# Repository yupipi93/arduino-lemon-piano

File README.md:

<div align="center">

# 🍋 Super Lemon Piano

**Seven lemons, an Arduino Nano and a secret Mario melody.**
A 2019 university project, rescued in 2026 and still growing — nine boards, a
fabricable PCB, a printed case, and a firmware that is tested on a fake board
before it ever touches fruit.

</div>

---

## What it is

Hold a ground clip in one hand and touch a lemon with the other: your body closes
the circuit, the pin drops **three or four ADC counts**, and a note sounds. Seven
lemons make a keyboard. Each of the **four levels** hides a ten-note Mario melody
— the game plays you the hook, you find the notes, and ten green LEDs count how
close you are. Get it and the whole theme plays as a celebration; miss and the bar
blanks and you start that level again. There is also a fifth mode with no game in
it at all, where the lemons are simply *do re mi fa sol la si*.

The repo is organised as **one directory per hardware revision, all of them
active**. Nothing is archived: a bare-buzzer bring-up rig, the 2019 banana-piano
original, the water-pump build that was handed in at university, and today's
filtered ten-LED board each keep their own firmware, wiring diagram, emulation and
docs — and each is expected to build.

| Read | For |
|---|---|
| [**USER-GUIDE.md**](docs/USER-GUIDE.md) · [en español](docs/GUIA-DE-USO.es.md) | Playing it. The printable sheet — no electronics in it |
| [**versions/**](versions/) | The nine boards, what changed between them, and why |
| [**pcb/**](pcb/) | The fabricable KiCad 9 board, its renders and its gerbers |
| [**docs/HARDWARE.md**](docs/HARDWARE.md) | Touch physics, the polarity flip, the shared parts |
| [**docs/MARIO-SOUNDS.md**](docs/MARIO-SOUNDS.md) | Every melody and effect, with its provenance |
| [**docs/cartilla/**](docs/cartilla/) | The one-page folded booklet an organiser carries to an event |
| [**CHANGELOG.md**](CHANGELOG.md) · [TODO.md](TODO.md) | What changed, and what is still open |

---

## The thing itself

<div align="center">

<br/><em><b>SUPER LEMON PIANO</b> — printed case, ten-LED bar, passive buzzer behind the grille,<br/>two sensitivity buttons on the front, and a ribbon cable out to the fruit.</em>
</div>

<table>
<tr>
<td width="50%">

<br/><em>The ten LEDs run red → yellow → green, so how far you are is readable across a room. Left of the Nano: the 470 µF halves of the CLC pi filter.</em>
</td>
<td width="50%">

<br/><em>Seated in the case, with the Multitec logo embossed in the print. The ribbon leaves through a slot so the lid closes on a working piano.</em>
</td>
</tr>
</table>

### The PCB

<div align="center">

<br/><em>v0.7.1, top — LEDs north, keys south, Nano socketed with the USB facing west.</em>
<br/><br/>

<br/><em>Bottom — a full ground pour, and every 220 Ω pull-up on B.Cu.</em>
</div>

<div align="center">

<br/><em>Back from the fab house. <b>Created with ♥ by Multitec.</b></em>
</div>

---

## How it plays

1. **Power on.** The bar counts up while the firmware measures what *untouched*
   looks like on every lemon and derives the touch margin from the noise it finds.
   **Lights running = hands off the fruit.**
2. **It announces the level** with seven notes of that level's theme — and only
   notes your lemons can make (see *Three sizes of every song* below).
3. **Play.** Hold the GND clip, touch a lemon. The note sounds and holds for as
   long as you hold the fruit.
4. **Find the ten-note code.** Each correct note lights the next green LED. A
   wrong note blanks all ten and that level restarts. Nothing is punished until
   you have found the first note, so you can explore freely.
5. **Light all ten** and the level's **whole theme** plays as a celebration, then
   the flagpole fanfare, then the next level announces itself.
6. **Forgotten the tune?** **Tap the same lemon five times** and it plays again.

### The gestures

| Gesture | What it does |
|---|---|
| **tap +** / **tap −** | one step more / less sensitive — the bar shows where the knob sits |
| **hold + for 3 s** | switch between **free play** and the level you were on |
| **hold − for 3 s** | open the **mode wheel**: turn with + / −, accept with both buttons |
| **both buttons, 1 s**, while touching a lemon | **smart adjust** — learn the best margin from that real touch |
| **the same lemon ×5** | **play the level's tune again**. The note you just played counts as the first, so it is four more taps. It changes nothing: repeats never score |

### Free play

Hold **+** for three seconds and the game gets out of the way: the seven lemons
become `do re mi fa sol la si` (C5–B5), there is no code and no wrong note, and
**the same lemon may be played over and over** — which is exactly what the game
forbids, and exactly what an instrument is for.

The bar in free play **only ever moves**. Entering runs a sweep: two lights walk
in from the ends of the bar, meet in the middle, open back out until all ten are
lit, and go out. After that it is dark, and every note breaks a **wave** from that
lemon's own place on the bar — lemon 1 sends it left to right, lemon 7 right to
left, a lemon in the middle opens it both ways at once. Hold two lemons together
and both notes sound: one buzzer cannot hold two frequencies, so the voices swap
it every 10 ms, fast enough that the ear hears an interval instead of an
alternation.

### Three sizes of every song

Each theme exists at three lengths, because three different moments need three
different things:

| Size | Where | What it is |
|---|---|---|
| **Short** | the mode wheel | eight notes. Browsing four modes has to be fast |
| **Playable** | the level announcement, and the five-tap reminder | **seven notes, and only notes that level's lemons can make** |
| **Full** | the celebration when a level is cleared | the whole piece, 10–23 s |

The middle one is the clue, so it must not be full of notes the keyboard cannot
answer with — every theme reaches pitches that are on no lemon. The firmware
walks the theme, plays only what the level's row contains, and turns anything
else into silence of the same length so the rhythm of the hook survives. It lands
on each theme's actual hook, which is a pleasant accident of how Mario wrote them:

| Level | Theme | What it announces | The seven lemons, low → high |
|---|---|---|---|
| 1 | Overworld | `E7 E7 E7 C7 E7 G7 G6` — the riff, exactly | E6 G6 A6 B6 C7 E7 G7 |
| 2 | Underworld | `C4 C5 A3 A4 AS3 AS4 C4` | A3 AS3 C4 D4 A4 AS4 C5 |
| 3 | Starman | `C6 F5 F5 D5 F5 F5 D5` | C5 D5 E5 F5 G5 A5 C6 |
| 4 | Castle | `G3 D4 G3 D4 AS3 D4 AS3` — the pedal | G3 AS3 C4 D4 DS4 F4 G4 |

**Every lemon on every level is a note that level's own theme plays.** That is a
rule with a test behind it, not a convention — it was broken on levels 2, 3 and 4
until 2026-09-15, and level 4 answered a G-minor theme with a C major scale an
octave up.

<details>
<summary><b>The four secret codes (spoilers)</b></summary>

<br/>

Lemons numbered 1–7, left to right — lemon 1 is the one that sounds **lowest**.

| Level | Theme | Code |
|---|---|---|
| 1 | Super Mario Bros — Overworld | `6 · 5 · 6 · 7 · 2 · 5 · 2 · 1 · 3 · 4` |
| 2 | Super Mario Bros — Underworld | `3 · 6 · 1 · 4 · 2 · 5 · 3 · 6 · 1 · 4` |
| 3 | Super Mario Bros — Starman | `2 · 4 · 6 · 1 · 5 · 3 · 7 · 4 · 2 · 6` |
| 4 | Super Mario Bros — Castle | `5 · 1 · 3 · 7 · 2 · 6 · 4 · 1 · 5 · 3` |

Clear all four and the game-complete piece loops until you hold both buttons.

These numbers are **never typed by hand**. A level's code lives in the firmware as
note *frequencies*, and which lemon plays which note differs per level, so the
answer exists nowhere in the source. [`docs/cartilla/seqs.py`](docs/cartilla/seqs.py)
resolves one table against the other, cross-checks level 1 against a sequence the
host test declares independently, and exits non-zero rather than guess.

</details>

---

## The modes, as a machine

```mermaid
stateDiagram-v2
    direction LR
    state "FREE PLAY<br/>do re mi fa sol la si" as FreePlay
    state "MODE WHEEL<br/>four levels, previewed" as Wheel

    [*] --> Calibrate
    Calibrate --> Game : margin from measured noise

    state "GAME" as Game {
        [*] --> Level1
        Level1 --> Level2 : all ten LEDs
        Level2 --> Level3 : all ten LEDs
        Level3 --> Level4 : all ten LEDs
        Level4 --> Ending : all four cleared
        Ending --> Level1 : both buttons 1 s
    }

    Game --> FreePlay : hold + for 3 s
    FreePlay --> Game : hold + for 3 s
    Game --> Wheel : hold − for 3 s
    Wheel --> Game : both buttons = accept
    Wheel --> Game : long press = cancel
```

Free play is **chosen, never earned**: winning cycles 1 → 2 → 3 → 4 → 1 and never
lands on it.

---

## Hardware

<div align="center">

<br/><em>Every wiring diagram in this repo is <b>generated</b>, never hand-placed — see below.</em>
</div>

### Pin map (V5.5)

| Pin | What | Notes |
|---|---|---|
| `A0`–`A6` | lemon keys 1–7 | 220 Ω pull-up each; the player holds the **GND** clip |
| `D2`–`D11` | the ten-LED bar | LED *n* on pin *n+1* — nothing to look up |
| `D12` | **SENS +** button | to GND, internal pull-up |
| `A7` | **SENS −** button | analog-in only, so an external 10 kΩ pull-up; read as `< 512` |
| `D13` | passive buzzer | the Nano's own LED blinks with the audio, for free |

Needs a **Nano or Mini**: A6 is a key and A7 is a button, and the classic Uno
exposes neither.

### The board

| | |
|---|---|
| **Outline** | 120 × 40 mm, 2-layer FR4, 4 × M2 mounting |
| **MCU** | Arduino Nano, socketed, centred, mini-USB facing west |
| **Display** | 10 × Ø3 mm LEDs, north edge — 3 green, 3 yellow, 2 orange, 2 red |
| **Keys** | 1×8 header on the south edge, silk reads `KEYS 1 2 3 4 5 6 7 G` |
| **Sound** | passive buzzer + an `SPK` aux header in parallel with it |
| **Power** | `5V IN` → P6KE6.8A TVS → 1N5817 → 470 µF‖100 nF → 100 µH → 470 µF‖100 nF |
| **Status** | v0.7.1 — DRC 0/0/0, ERC 0/0, placement 74/0, geometry gate 30/30 |
| **Fab** | [`pcb/releases/v0.7.1/`](pcb/releases/v0.7.1/) — gerbers, drill, BOM, positions |

<details>
<summary><b>Why there is a filter on a 5 V input at all</b></summary>

<br/>

A touch is **3–4 ADC counts, about 15–20 mV** — skin is roughly 1 MΩ against a
220 Ω pull-up, which is a very lopsided divider. The +5 V rail is simultaneously
the top of all seven pull-ups **and AVcc, the ADC's own reference**. A slow sag
cancels out, because the ADC is ratiometric and baseline and reading move
together. A **fast edge does not**: the pin node sits behind 220 Ω and wire
capacitance while the reference goes straight into AVcc, so the two move at
different speeds and the difference lands squarely inside a 15 mV margin.

Which is not theory. A light switch elsewhere in the house played phantom notes.
The filter (TVS + Schottky + CLC pi, fc ≈ 730 Hz) is V5.5's entire hardware
delta; the game and the firmware pinout are V5's, untouched.

Full derivation: [`versions/v5.5-power-filter/HARDWARE.md`](versions/v5.5-power-filter/HARDWARE.md).
Running it off a battery instead: [`docs/POWER-FROM-A-POWER-BANK.md`](docs/POWER-FROM-A-POWER-BANK.md).

</details>

---

## Quick start

```bash
# PlatformIO CLI, once
pipx install platformio                 # or: pip install --user platformio

cd versions/v5.5-power-filter/firmware  # ...or any other version's firmware/
pio run                                 # build  (default: nanoatmega328)
pio run -t upload                       # flash the Nano
pio device monitor                      # 9600 baud — the game logs what it is doing
```

No hardware is needed to build: `pio run` is the compile check every commit goes
through, and **every version in this repo still builds**, including the 2019
sketches.

```bash
bash versions/v5.5-power-filter/firmware/test/run.sh   # 281 checks, plain g++, exit 0
python3 tools/wiring_diagrams.py                       # re-render every wiring diagram
python3 docs/cartilla/seqs.py                          # re-derive the four codes
```

<details>
<summary><b>Upload fails, or something sounds wrong</b></summary>

<br/>

**"programmer is not responding"** — most 2019-era Nano clones carry the old
bootloader (57600 baud) and newer ones the new one (115200):

```bash
pio run -e nanoatmega328new -t upload
```

**The sound is suspect** — flash [**V0**](versions/v0-buzzer/), a board with
nothing on it but the buzzer, playing a scale forever on the same pin every
version uses. It removes the keyboard, the sensing and the game in one step:

```bash
cd versions/v0-buzzer/firmware && pio run -t upload && pio device monitor
```

**Touches register wrongly, or not at all** — flash
[**V2.5**](versions/v2.5-threshold-buttons/): V2's keyboard plus two buttons that
move the touch threshold live, with a serial readout of all seven channels
against it. Or build V5.5 with `-DDEBUG_TOUCH`, which prints every channel's dip
four times a second while a lemon is held.

</details>

---

## The nine boards

The numbers follow the **boards, not the calendar**: V4.5 is V4 minus the pump
plus two buttons, so it sits before V5 even though it was wired later.

| # | Version | Hardware delta | Firmware | Emulation |
|---|---|---|---|---|
| 0 | [**V0** — buzzer rig](versions/v0-buzzer/) | *bring-up (2026)*: one passive buzzer and nothing else | ✅ | ✅ |
| 1 | [**V1** — banana piano](versions/v1-banana-piano/) | *the 2019 origin*: 7 fruit keys, 220 Ω pull-ups, HC-SR04 | ✅ | — |
| 2 | [**V2** — keyboard test](versions/v2-keyboard-test/) | − HC-SR04: the keyboard and speaker alone | ✅ | — |
| 2.5 | [**V2.5** — live threshold](versions/v2.5-threshold-buttons/) | + 2 buttons that move the touch threshold **while it runs** | ✅ | ✅ |
| 3 | [**V3** — game prototype](versions/v3-game-prototype/) | + feedback LEDs, game-select button, one relay — the game is born | ✅ | — |
| 4 | [**V4** — water pump](versions/v4-water-pump/) | clip flips to +5 V, 2nd relay + **water pump**, RESTART | ✅ | ✅ |
| 5 | [**V4.5** — margin buttons](versions/v4.5-margin-buttons/) | − relays and pump · + MARGIN +/− buttons | ✅ | ✅ |
| 6 | [**V5** — LED bar](versions/v5-led-bar/) | keyboard back to pull-ups + GND clip · + **ten LEDs** | ✅ | ✅ |
| 7 | [**V5.5** — power filter](versions/v5.5-power-filter/) ⭐ | + **filtered 5 V input**. The board this repo is about | ✅ | ✅ + host tests |
| 8 | [**V6** — battery + amp](versions/v6-battery-amp/) 📐 | *proposal only*: LiPo + power-bank module, LM386 + speaker | — | — |

The rule for adding one, and the checklist: [`docs/VERSIONING.md`](docs/VERSIONING.md).

---

## How this repo keeps itself honest

**The firmware is tested on a fake board.** `test/piano_sim_test.cpp` compiles
`src/main.cpp` *verbatim* against a stand-in AVR runtime with virtual time, seven
analog touch channels with noise and **channel coupling**, two buttons and ten
LEDs — then plays the piano and asserts what came out. It models the ADC's
sample-and-hold settling on a 1 MΩ source, flaky finger contact, and one finger
shadowing its neighbours, because all three have caused real bugs. It records the
LED bar as a **film** rather than a snapshot, so animations are assertable, and it
counts buzzer pin edges, because themes are bit-banged and leave no other trace.

**281 checks, 0 failed.** It has caught, among others: a gesture that would have
fired on every note on a coupled rig, a chord that could never be released, and a
level whose lemons were in the wrong key.

**Every wiring diagram is generated.** [`tools/wiring_diagrams.py`](tools/wiring_diagrams.py)
is a declarative contract — components, positions, nets — consumed by the
**wirewright** auto-router and DRC engine. No wire crosses a component, overlaps
another net, or leaves a pin unconnected, because the renderer refuses.

**The PCB is generated and gated too.** Place, route, DRC, render and fab outputs
come from the sibling `eda-pcb-designer` toolkit, and a release only exists if
DRC, ERC, placement and a geometry gate all pass.

---

## Take it to an event

<table>
<tr>
<td width="42%" align="center">

<br/><em><a href="docs/poster/">The poster</a> — stored byte for byte,<br/>hash-pinned so a later re-encode is visible.</em>
</td>
<td width="58%">

**The booklet.** One A4 sheet, black and white, folded down the middle into an
A5: the cover, what the two buttons do, *si algo va mal*, how the game works, and
the four codes. Almost no prose — nearly every explanation is a drawing of the
**LED bar itself**, ten boxes filled or empty, because that is the only thing the
piano can say and the only thing a helper has to read.

It exists so someone who has never seen the lemon piano can switch it on, explain
it and rescue it with nobody technical in the room.

```bash
docs/cartilla/build.sh      # re-derives the codes from the firmware, then renders
```

→ [`docs/cartilla/`](docs/cartilla/)

</td>
</tr>
</table>

---

## Status

- **V5.5 is built, cased and playing.** Firmware 17 998 B (58.6 % flash),
  558 B RAM (27.2 %), flashed and verified.
- **Open, and honest about it:** the chord's gates and the free-play wave timing
  are tuned from the physics and from host tests, and still want a session with
  fingers on real fruit. The `-DDEBUG_TOUCH` build prints the numbers needed to
  settle both. See [TODO.md](TODO.md) items 21–23.
- **The Velxio browser emulation** covers V0, V2.5, V4, V4.5 and V5; V5.5's own
  spec is written but has never had a `--mode verify` pass, because the harness is
  not installed on the machine it was written on.
- **No LICENSE file yet.** Ask before reusing.

---

<div align="center">

**Author:** Yupipi93 (Sergio Conejero), 2019
**Rescued, reworked, documented and tested with Claude,** 2026
Built at [**Multitec**](https://multitecua.com) 🍋

</div>

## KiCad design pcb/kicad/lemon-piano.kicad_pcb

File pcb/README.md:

# Lemon Piano V5.5 Board

A fabricable 2-layer KiCad-9 PCB that replaces the
[V5.5](../versions/v5.5-power-filter) breadboard build of this repo — same circuit, same firmware pinout, nothing invented. Seven lemon
touch keys, a ten-LED progress bar, two sensitivity buttons, a passive
buzzer, and the V5.5 **power-entry filter** (TVS + Schottky + CLC pi) that
keeps mains transients from playing phantom notes on a 15–20 mV touch
margin.

| | |
|---|---|
| Realistic (3D bodies) |  |
| Photo overlay (real Nano photo, dimensioned) |  |
| Normal (bare copper/silk) |  |
| DIM plot (front) |  |
| Bottom (realistic) |  |

Per version the pipeline archives four styles per side under `renders/`
(`<ver>-{normal,dim,realistic,overlay}-{top,bottom}.png`), all produced
by the hosted pcb-designer API; the overlay composites the real Arduino
Nano photo (Wikimedia Commons, CC BY 2.0) that the pipeline uploads from
`overlays/component-images/` + `overlays/modules.yaml`. Every socket pin
carries its function on silk (MT1-style legends) and every component its
reference, both layers.

## At a glance

| Item | Value |
|---|---|
| Outline | **120 × 40 mm**, 2-layer FR4, MT1 coordinate frame (x 90–210, y 100–140, centre 150/120) |
| MCU | Arduino Nano (ATmega328P), **socketed, centred, mini-USB facing WEST** — 2×15-pin 2.54 mm rows (pin field x 132.22–167.78, rows y 112.38/127.62). USB-west puts the digital column on the north row and the analog column on the south row (LEDs north / keys south, ADR-035), and a **part-free cable corridor** (x < 130.4, y 113–127) lets the cable plug in with the module seated — for the enclosure. USB 5 V still stays behind the 1N5817 |
| Keys | 7 lemon lines (A0–A6, 220 Ω pull-ups on B.Cu) + GND clip → labelled 1×8 header **centred** on the **SOUTH** edge, pin 1 = KEY1 at the west so silk reads `KEYS 1 2 3 4 5 6 7 G` west→east (pin centre exactly x=150; the fan under A0..A6 does not cross, ADR-036) |
| Display | 10 × 3 mm LEDs (D2–D11): 3 green → 3 yellow → 2 orange → 2 red, **NORTH** edge, **centred on x=150**, **LED1 at the EAST** (the bar fills right→left with the USB on the left — it follows D2..D11, which descend west→east, ADR-036/021), 220 Ω each on B.Cu |
| Controls | SENS+ (D12) / SENS− (A7 + 10 k pull-up) buttons in the EAST block, the **pair centred on the y=120 mid-line**, each with a **parallel 2-pin header** (J3/J4) for an external panel button (ADR-026) |
| Sound | passive buzzer on D13, NE corner — ~60 mm from its pin (D13 is at the west end again; accepted in ADR-027). **`SPK`** (J5) is a 2-pin aux output wired in parallel with it (ADR-034) |
| Power | `5V IN` **2-pin header** → P6KE6.8A TVS → 1N5817 → 470 µF‖100 nF → 100 µH → 470 µF‖100 nF → +5 V rail (≈4.7 V, fc ≈ 730 Hz). Whole filter in the WEST block folded around the USB corridor: **C1 ‖ C3 adjacent** on the north row, D2 / J1 → D1 / L1 in the south strip (ADR-025/031/037) |
| GND | full B.Cu zone, solid connect on every GND pad, auto island-healing |
| Mounting | 4 × M2 (Ø2.5 drill / Ø5.0 pad+vias): two per short edge at x=95/205, y=105/135 — mirror-symmetric about x=150 and y=120 |
| Silk (v0.7.1) | **"Created with ♥ by Multitec."** maker's mark filling the top-left free rectangle (heart drawn as a filled silk polygon — the stroke font has no ♥ glyph); ADR-038 |
| Status (v0.7.1) | DRC **0/0/0** · ERC 0/0 · verify_placement 74/0 · verify_holes (+vision) · geometry_gate 30/30 ALL PASS |
| Release | [`releases/v0.7.1/lemon-piano-v0.7.1-fab.zip`](releases/v0.7.1/) — gerbers, drill, BOM, positions |

**Implementing a change?** Paste [docs/AGENT_PROMPT.md](docs/AGENT_PROMPT.md)
into a fresh agent session together with the change request — it encodes
the full workflow, gates and pitfalls learned across v0.0.1→v0.7.1.

Netlist ground truth: [docs/NETLIST.md](docs/NETLIST.md) ·
decisions: [docs/DECISIONS.md](docs/DECISIONS.md) ·
state + iteration log: [docs/DESIGN_STATE.md](docs/DESIGN_STATE.md) ·
render history: [renders/INDEX.md](renders/INDEX.md)

## How to regenerate

Everything is generated from [`lemon-piano.yaml`](lemon-piano.yaml) +
[`docs/NETLIST.md`](docs/NETLIST.md). The pcb-designer toolkit lives in the
sibling repo `../eda-pcb-designer` (its Docker image + hosted API); the
cloud service does every
pipeline operation that has an endpoint, the Docker image handles the two
generative steps (board/schematic instantiation) and the width/zone
post-pass:

```bash
# one full iteration: build → /place → /route → post → /drc → /render → gates
./pcb/tools/cloud_pipeline.sh v0.7.1

# release (adds cloud /fab, writes releases/<ver>/):
./pcb/tools/cloud_pipeline.sh v0.7.1 --fab

# render variants (any style, hosted API):
URL=https://pcb-designer.scv.multitecua.com
curl -F pcb=@pcb/kicad/lemon-piano.kicad_pcb "$URL/render?side=both&style=realistic" -o r.zip
curl -F pcb=@pcb/kicad/lemon-piano.kicad_pcb -F modules=@pcb/overlays/modules.yaml \
     -F images=@pcb/overlays/component-images/arduino-nano.png \
     "$URL/render?side=top&style=overlay&calibration=green_bbox" -o overlay.png

# individual gates:
python3 pcb/tools/verify_placement.py   # anti-mirror/pin-swap
python3 pcb/tools/verify_holes.py       # anchor holes vs GT
python3 pcb/tools/geometry_gate.py      # outline/symmetry/copper
```

All builders are idempotent — re-running produces byte-identical files
(LESSONS_LEARNED §7). The KiCad artefacts live in `kicad/`; every
iteration's DRC report and renders are archived under `validation/` and
`renders/` with their version tag.

## Look at the board in 3D

Every pipeline run writes a rotatable model to `pcb/3d/`, **committed to the
repo** so you can clone and look at the board with no KiCad toolchain at all:

| File | For |
|---|---|
| `lemon-piano-<ver>.glb` | looking at it: browsers, `f3d`, Windows/macOS 3D viewers |
| `lemon-piano-<ver>.step` | CAD — FreeCAD / Fusion, enclosure fit checks |

**In VS Code — one click.** This repo ships a
[`.vscode/extensions.json`](../.vscode/extensions.json) recommending
[`thingraph.cad-viewer`](https://marketplace.visualstudio.com/items?itemName=thingraph.cad-viewer),
so VS Code offers to install it the first time you open the project
(Extensions view → *Recommended*). Or explicitly:

```bash
code --install-extension thingraph.cad-viewer
```

Then **double-click `pcb/3d/lemon-piano-v0.7.1.glb`** — or the `.step` — and it
opens in a tab you can drag to rotate. It is the only extension that handles
both formats the pipeline emits, and it bundles `occt-import-js.wasm`
(OpenCascade), so STEP is a real geometry kernel. Free, read-only, ~24 MB.

> Don't reach for **glTF Tools** (`cesium.gltf-vscode`) instead just because it
> has 100× the installs: it validates and converts glTF/GLB but registers no
> viewer for `.glb`, so you'd have to import to `.gltf` first to see anything.

**Web, nothing to install** — open <https://3dviewer.net> and drag the `.glb`
in. Drag rotates, scroll zooms. It renders in your browser, so the file is not
uploaded to a server.

**Local, lightweight** — [f3d](https://f3d.app):

```bash
sudo apt install f3d
f3d pcb/3d/lemon-piano-v0.7.1.glb
```

Note these are binaries in git (~16 MB per version, and git history keeps
every past one forever — deleting them later does not shrink the repo). That
is a deliberate trade: the files are the whole point of having them, and a
handful of releases is well inside GitHub's limits. If it ever gets heavy, the
standard fix is Git LFS, not deletion. Only `pcb/3d/models/` stays untracked —
that is the fetched cache of verbatim third-party KiCad body files, which the
script re-downloads in seconds.

They will **not** preview on github.com: GitHub renders only `.stl` inline and
only up to 10 MB, and this board's STL is 34 MB. Download the `.glb` and open
it with one of the viewers above.

Generated by the cloud `/export3d` endpoint during
`cloud_pipeline.sh`, because the service image ships the `kicad-packages3d`
body library that the slim local Docker image deliberately omits. To make them
without the pipeline (fetches just the ~15 bodies this board needs, ~1.4 MB,
cached in `pcb/3d/models/`):

```bash
./pcb/tools/export_3d.sh
```

Note the two orange LEDs (D9/D10) show **red** in locally generated files —
no orange body exists in the upstream library, so the exporter falls back to
the base one and says so. The cloud-generated files have the real orange.

**KiCad's own viewer** is the richest option (layer toggles, cross-sections,
raytracing) but needs KiCad 9 installed. Ubuntu's repos only carry KiCad 7,
which cannot open this v9 board — use the PPA, and stay on the 9.x series so
the file format keeps matching the pipeline:

```bash
sudo add-apt-repository ppa:kicad/kicad-9.0-releases
sudo apt update && sudo apt install --install-recommends kicad kicad-packages3d
```

Then open `pcb/kicad/lemon-piano.kicad_pcb` and press **Alt+3**.

## Assembly notes

- Small passives are 0805 HandSolder; R1–R7/R18 and R8–R17 + C2/C4 mount
  on the **bottom** (refs on F.Fab, values in the BOM/pos files).
- Feed `5V IN` (J1, `+` west / `−` east) from a USB wall charger or bench
  supply — never the PC that flashes the Nano (see the V5.5 powering
  rules); loop the input lead 3–4 turns through a clip-on ferrite for the
  common-mode path. J1 is a bare header, so strain-relieve the input lead
  (zip-tie through a mounting hole) if the piano gets carried around.
- The GND terminal position (`G`, **east** end of the keys header, next to
  key 7) is the player's hand-held clip line.
- `EXT+` (J3) and `EXT−` (J4) are wired in parallel with the SENS+/SENS−
  buttons. Leave them empty for on-board-only use, or wire a panel button
  across each pair — no jumper to move, and both buttons keep working.
- **`SPK` (J5) is the aux sound output**, in parallel with the buzzer: pin 1
  is the raw D13 drive, pin 2 is GND. The on-board buzzer keeps sounding
  either way. **Mind the load** — D13 drives a *passive piezo* directly, so
  J5 suits another piezo element or an **amplified** speaker module
  (PAM8403 / LM386 board / powered PC speakers, all high-impedance inputs).
  A bare 4–8 Ω speaker would draw ~600 mA against the ATmega328P's 40 mA
  absolute maximum per pin and **would damage D13** — drive one only through
  an amplifier (ADR-034).
- **Flashing with the Nano seated.** The mini-USB faces WEST into a part-free
  corridor (x < 130.4, y 113–127 — ADR-035), so the cable plugs in past the
  C1/C3 row above and the D2/L1 parts below and leaves the board on the left,
  nowhere near the SENS buttons. Plan the enclosure's cut-out on that side.
  Tracks do run through the corridor (that is fine); never place a part there.
- **The VU meter fills right→left** when the USB is on your left: LED 1
  (green) is at the east end, LED 10 (red) at the west (ADR-036 — the bar
  follows the D2..D11 pins so no traces cross). Flip the board's orientation
  in the enclosure if you want green on the left, or ask for the reversed
  bar (a YAML change + re-route).

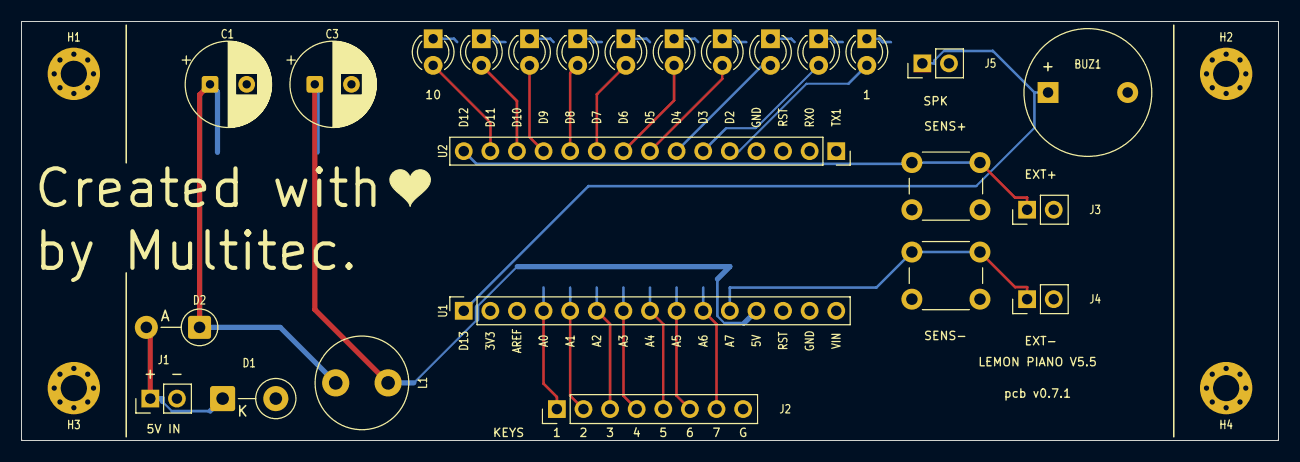
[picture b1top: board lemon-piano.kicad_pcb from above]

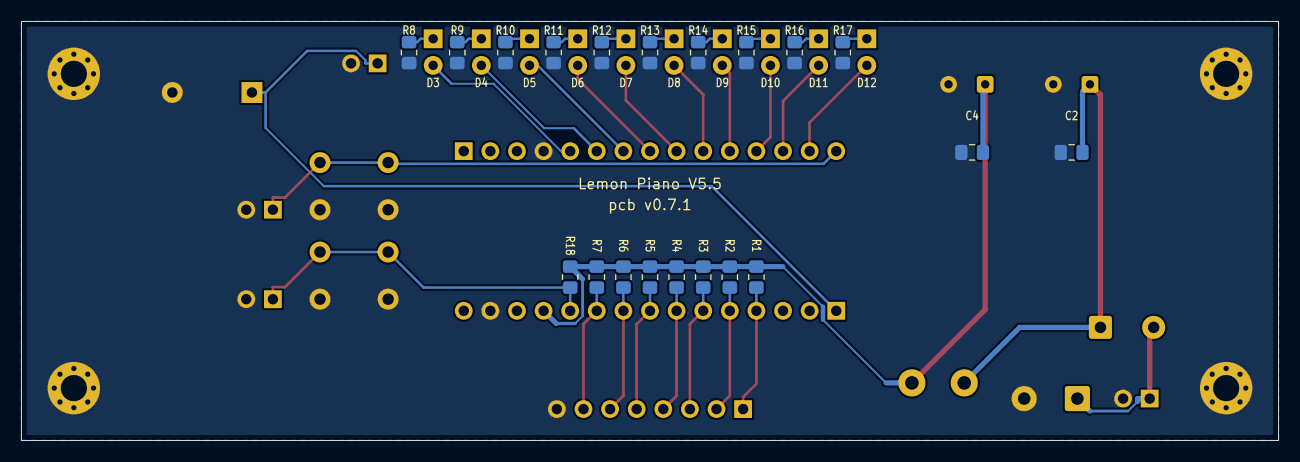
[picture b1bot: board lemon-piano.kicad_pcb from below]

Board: 2 copper layers, 120.0 x 40.0 mm, 49 parts (20 on the bottom side), 34 nets.

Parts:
BUZ1: passive_buzzer; Buzzer_12x9.5RM7.6
C1, C3: 470uF/16V; CP_Radial_D8.0mm_P3.50mm
C2, C4: 100nF; C_0805_2012Metric_Pad1.18x1.45mm_HandSolder
D1: P6KE6.8A; D_DO-15_P5.08mm_Vertical_KathodeUp
D2: 1N5817; D_DO-41_SOD81_P5.08mm_Vertical_AnodeUp
D3, D4, D5: GREEN; LED_D3.0mm
D6, D7, D8: YELLOW; LED_D3.0mm
D9, D10: ORANGE; LED_D3.0mm
D11, D12: RED; LED_D3.0mm
H1, H2, H3, H4: M2; MountingHole_2.5mm_Pad_Via
J1: 5V_IN; PinHeader_1x02_P2.54mm_Vertical
J2: LEMON_KEYS; PinHeader_1x08_P2.54mm_Vertical
J3: SENS+_EXT; PinHeader_1x02_P2.54mm_Vertical
J4: SENS-_EXT; PinHeader_1x02_P2.54mm_Vertical
J5: SPK_OUT; PinHeader_1x02_P2.54mm_Vertical
L1: 100uH; L_Radial_D8.7mm_P5.00mm_Fastron_07HCP
R1, R2, R3, R4, R5, R6, R7, R8, R9, R10, R11, R12, R13, R14, R15, R16, R17: 220; R_0805_2012Metric_Pad1.20x1.40mm_HandSolder
R18: 10k; R_0805_2012Metric_Pad1.20x1.40mm_HandSolder
SW1: SENS+; SW_PUSH_6mm
SW2: SENS-; SW_PUSH_6mm
U1: Nano_socket_A; PinSocket_1x15_P2.54mm_Vertical
U2: Nano_socket_B; PinSocket_1x15_P2.54mm_Vertical

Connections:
/+5V: C3.1, C4.1, L1.2, R1.2, R2.2, R3.2, R4.2, R5.2, R6.2, R7.2, R18.2, U1.12
/BUZZER: BUZ1.1, J5.1, U1.1
/GND: BUZ1.2, C1.2, C2.2, C3.2, C4.2, D1.2, H1.1, H2.1, H3.1, H4.1, J1.2, J2.8, J3.2, J4.2, J5.2, R8.1, R9.1, R10.1, R11.1, R12.1, R13.1, R14.1, R15.1, R16.1, R17.1, SW1.2, SW2.2, U1.14, U2.4
/KEY1: J2.1, R1.1, U1.4
/KEY2: J2.2, R2.1, U1.5
/KEY3: J2.3, R3.1, U1.6
/KEY4: J2.4, R4.1, U1.7
/KEY5: J2.5, R5.1, U1.8
/KEY6: J2.6, R6.1, U1.9
/KEY7: J2.7, R7.1, U1.10
/LED1: D3.2, U2.5
/LED1_K: D3.1, R8.2
/LED2: D4.2, U2.6
/LED2_K: D4.1, R9.2
/LED3: D5.2, U2.7
/LED3_K: D5.1, R10.2
/LED4: D6.2, U2.8
/LED4_K: D6.1, R11.2
/LED5: D7.2, U2.9
/LED5_K: D7.1, R12.2
/LED6: D8.2, U2.10
/LED6_K: D8.1, R13.2
/LED7: D9.2, U2.11
/LED7_K: D9.1, R14.2
/LED8: D10.2, U2.12
/LED8_K: D10.1, R15.2
/LED9: D11.2, U2.13
/LED9_K: D11.1, R16.2
/LED10: D12.2, U2.14
/LED10_K: D12.1, R17.2
/SENS_MINUS: J4.1, R18.1, SW2.1, U1.11
/SENS_PLUS: J3.1, SW1.1, U2.15
/VIN: D1.1, D2.2, J1.1
/VRAW: C1.1, C2.1, D2.1, L1.1

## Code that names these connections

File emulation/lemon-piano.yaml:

name: lemon-piano
description: >
  Interactive Velxio emulation of the Lemon Piano V5. The 7 lemons are
  clickable pushbuttons (keys 1-7 on A0-A5 + D12 — the VELXIO_EMULATION input
  shim in firmware/src/main.cpp, see emulation/README.md). A row of TEN green
  LEDs (D2,D3,D4,D5,D6,D7,D8,D9,D10,D13) is the progress bar: each correct note
  lights the next LED, a wrong note blanks them all. Buzzer on D11 plays through
  the browser's speakers. There is no game-select switch or restart button (no
  pins left beside 10 LEDs): the browser starts at game 1 (Mario Main Theme) and
  each win AUTO-ADVANCES to the other theme. Verify mode plays game 1's secret
  code by injecting timed key presses and asserts WIN + the flip to Game 2.
board: arduino-nano
sketch_file: ../firmware/src/main.cpp
defines: [VELXIO_EMULATION]
extra_files:
  - name: notes.h
    file: ../firmware/include/notes.h

components:
  # ── The 7 "lemons": one horizontal piano row. Labels "1".."7" double as the
  # PC-keyboard mapping (frontend patch 0002). Each key's 10k pull-up sits in
  # the resistor row above it; the board signal wire ends at the resistor, never
  # at button level, so no cable crosses the buttons.
  - { id: key1, type: pushbutton, x: 60,  y: 430, properties: { color: "yellow", label: "1" } }
  - { id: key2, type: pushbutton, x: 190, y: 430, properties: { color: "yellow", label: "2" } }
  - { id: key3, type: pushbutton, x: 320, y: 430, properties: { color: "yellow", label: "3" } }
  - { id: key4, type: pushbutton, x: 450, y: 430, properties: { color: "yellow", label: "4" } }
  - { id: key5, type: pushbutton, x: 580, y: 430, properties: { color: "yellow", label: "5" } }
  - { id: key6, type: pushbutton, x: 710, y: 430, properties: { color: "yellow", label: "6" } }
  - { id: key7, type: pushbutton, x: 840, y: 430, properties: { color: "yellow", label: "7" } }
  # Pull-ups (10k to 5V) — REQUIRED: an active-low button with no pull-up floats
  # at ~0V in the solver and reads permanently pressed. One per key column
  # (pin 1 = left = 5V bus, pin 2 = right = key node).
  - { id: rp1, type: resistor, x: 36,  y: 310, properties: { value: "10000" } }
  - { id: rp2, type: resistor, x: 166, y: 310, properties: { value: "10000" } }
  - { id: rp3, type: resistor, x: 296, y: 310, properties: { value: "10000" } }
  - { id: rp4, type: resistor, x: 426, y: 310, properties: { value: "10000" } }
  - { id: rp5, type: resistor, x: 556, y: 310, properties: { value: "10000" } }
  - { id: rp6, type: resistor, x: 686, y: 310, properties: { value: "10000" } }
  - { id: rp7, type: resistor, x: 816, y: 310, properties: { value: "10000" } }
  # ── The ten-LED progress bar: a column on the far right, clear of the
  # keyboard. Series resistor (D-pin -> anode) then LED, cathode to the GND
  # chain. LED n lights after the n-th correct note.
  - { id: rl1,  type: resistor, x: 1010, y: 55,  properties: { value: "220" } }
  - { id: led1, type: led,      x: 1180, y: 40,  properties: { color: "green", label: "1" } }
  - { id: rl2,  type: resistor, x: 1010, y: 125, properties: { value: "220" } }
  - { id: led2, type: led,      x: 1180, y: 110, properties: { color: "green", label: "2" } }
  - { id: rl3,  type: resistor, x: 1010, y: 195, properties: { value: "220" } }
  - { id: led3, type: led,      x: 1180, y: 180, properties: { color: "green", label: "3" } }
  - { id: rl4,  type: resistor, x: 1010, y: 265, properties: { value: "220" } }
  - { id: led4, type: led,      x: 1180, y: 250, properties: { color: "green", label: "4" } }
  - { id: rl5,  type: resistor, x: 1010, y: 335, properties: { value: "220" } }
  - { id: led5, type: led,      x: 1180, y: 320, properties: { color: "green", label: "5" } }
  - { id: rl6,  type: resistor, x: 1010, y: 405, properties: { value: "220" } }
  - { id: led6, type: led,      x: 1180, y: 390, properties: { color: "green", label: "6" } }
  - { id: rl7,  type: resistor, x: 1010, y: 475, properties: { value: "220" } }
  - { id: led7, type: led,      x: 1180, y: 460, properties: { color: "green", label: "7" } }
  - { id: rl8,  type: resistor, x: 1010, y: 545, properties: { value: "220" } }
  - { id: led8, type: led,      x: 1180, y: 530, properties: { color: "green", label: "8" } }
  - { id: rl9,  type: resistor, x: 1010, y: 615, properties: { value: "220" } }
  - { id: led9, type: led,      x: 1180, y: 600, properties: { color: "green", label: "9" } }
  - { id: rl10, type: resistor, x: 1010, y: 685, properties: { value: "220" } }
  - { id: led10,type: led,      x: 1180, y: 670, properties: { color: "green", label: "10" } }
  # Buzzer, far right and clear of the LED column.
  - { id: buzzer1, type: buzzer, x: 1360, y: 40, properties: {} }

wires:
  # Signal columns: board pin -> resistor (key node) -> key leg.
  - [board:A0, rp1:2]
  - [rp1:2, key1:1.l]
  - [board:A1, rp2:2]
  - [rp2:2, key2:1.l]
  - [board:A2, rp3:2]
  - [rp3:2, key3:1.l]
  - [board:A3, rp4:2]
  - [rp4:2, key4:1.l]
  - [board:A4, rp5:2]
  - [rp5:2, key5:1.l]
  - [board:A5, rp6:2]
  - [rp6:2, key6:1.l]
  - [board:12, rp7:2]          # A6 has no digital pin; key 7 lives on D12
  - [rp7:2, key7:1.l]
  # 5V bus: chain along the resistor tops, one drop to the board.
  - [board:5V, rp1:1]
  - [rp1:1, rp2:1]
  - [rp2:1, rp3:1]
  - [rp3:1, rp4:1]
  - [rp4:1, rp5:1]
  - [rp5:1, rp6:1]
  - [rp6:1, rp7:1]
  # GND bus: daisy-chain along the button bottom legs, one drop to the board.
  - [board:GND.1, key1:2.l]
  - [key1:2.r, key2:2.l]
  - [key2:2.r, key3:2.l]
  - [key3:2.r, key4:2.l]
  - [key4:2.r, key5:2.l]
  - [key5:2.r, key6:2.l]
  - [key6:2.r, key7:2.l]
  # Ten-LED bar: each D-pin -> series resistor -> LED anode.
  - [board:2,  rl1:1]
  - [rl1:2,  led1:A]
  - [board:3,  rl2:1]
  - [rl2:2,  led2:A]
  - [board:4,  rl3:1]
  - [rl3:2,  led3:A]
  - [board:5,  rl4:1]
  - [rl4:2,  led4:A]
  - [board:6,  rl5:1]
  - [rl5:2,  led5:A]
  - [board:7,  rl6:1]
  - [rl6:2,  led6:A]
  - [board:8,  rl7:1]
  - [rl7:2,  led7:A]
  - [board:9,  rl8:1]
  - [rl8:2,  led8:A]
  - [board:10, rl9:1]
  - [rl9:2,  led9:A]
  - [board:13, rl10:1]
  - [rl10:2, led10:A]
  # LED cathodes daisy-chain down the column to GND.
  - [led1:C, led2:C]
  - [led2:C, led3:C]
  - [led3:C, led4:C]
  - [led4:C, led5:C]
  - [led5:C, led6:C]
  - [led6:C, led7:C]
  - [led7:C, led8:C]
  - [led8:C, led9:C]
  - [led9:C, led10:C]
  - [led10:C, board:GND.2]
  # Buzzer — on D11 (PWM-duty polled); the emulation firmware clears OCR2A after
  # each note (emuTone) so the note-off actually fires. On D8 it would beep forever.
  - [board:11, buzzer1:1]
  - [buzzer1:2, board:GND.2]

# Headless gameplay: after boot the browser starts at game 1 (Mario Main Theme),
# secret code 6,5,6,7,2,5,2,1,3,4 -> key pins A5,A4,A5,D12,A1,A4,A1,A0,A2,A3 =
# 19,18,19,12,15,18,15,14,16,17. Active-low pulses 350ms apart.
inputs:
  - { at_s: 2.00, press_pin: 19, hold_s: 0.08 }   # key 6
  - { at_s: 2.35, press_pin: 18, hold_s: 0.08 }   # key 5
  - { at_s: 2.70, press_pin: 19, hold_s: 0.08 }   # key 6
  - { at_s: 3.05, press_pin: 12, hold_s: 0.08 }   # key 7
  - { at_s: 3.40, press_pin: 15, hold_s: 0.08 }   # key 2
  - { at_s: 3.75, press_pin: 18, hold_s: 0.08 }   # key 5
  - { at_s: 4.10, press_pin: 15, hold_s: 0.08 }   # key 2
  - { at_s: 4.45, press_pin: 14, hold_s: 0.08 }   # key 1
  - { at_s: 4.80, press_pin: 16, hold_s: 0.08 }   # key 3
  - { at_s: 5.15, press_pin: 17, hold_s: 0.08 }   # key 4 -> WIN

assertions:
  - { type: serial_contains, pattern: "Lemon Piano V5", within_s: 3 }
  - { type: serial_contains, pattern: "Game 1",         within_s: 3 }
  - { type: gpio_toggles, pin: 2,  min_edges: 1,   within_s: 8 }   # LED 1 lit on first correct
  - { type: gpio_toggles, pin: 11, min_edges: 100, within_s: 14 }  # buzzer sang (keys + victory theme)
  - { type: serial_contains, pattern: "WIN",            within_s: 8 }
  # Victory light show: the bar flashes per note — LED 10 (D13) only ever
  # lights during the win, so >=40 edges proves the beat-synced blinking.
  - { type: gpio_toggles, pin: 13, min_edges: 40,  within_s: 16 }
  - { type: serial_contains, pattern: "Game 2",         within_s: 16 }  # auto-advanced after the theme

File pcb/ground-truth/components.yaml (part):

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    mount_side: top
    source: "user spec 2026-07-30 — a parallel 2-pin header per SENS button"
    pins:
      "J3.1": {func: pin, net: /SENS_PLUS}
      "J3.2": {func: gnd, net: /GND}
      "J4.1": {func: pin, net: /SENS_MINUS}
      "J4.2": {func: gnd, net: /GND}

  # Auxiliary speaker output, wired in PARALLEL with the buzzer (v0.6.0,
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    mount_side: bottom
    source: "v5 HARDWARE.md — 220R pull-up per key, pin->R->+5V"
    pins:
      "R1.1": {func: pin,  net: /KEY1}
      "R1.2": {func: rail, net: /+5V}
      "R2.1": {func: pin,  net: /KEY2}
      "R2.2": {func: rail, net: /+5V}
      "R3.1": {func: pin,  net: /KEY3}
      "R3.2": {func: rail, net: /+5V}
      "R4.1": {func: pin,  net: /KEY4}
      "R4.2": {func: rail, net: /+5V}
      "R5.1": {func: pin,  net: /KEY5}
      "R5.2": {func: rail, net: /+5V}
      "R6.1": {func: pin,  net: /KEY6}
      "R6.2": {func: rail, net: /+5V}
      "R7.1": {func: pin,  net: /KEY7}
      "R7.2": {func: rail, net: /+5V}

  SENS_MINUS_PULLUP:
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    mount_side: bottom
    source: "v5 HARDWARE.md — A7 has no internal pull-up: external 10k to +5V"
    pins:
      "R18.1": {func: pin,  net: /SENS_MINUS}
      "R18.2": {func: rail, net: /+5V}

  # ────────────────────────────────────────────────────────────────────
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    mount_side: top
    source: "v5 HARDWARE.md — SENS+ D12 to GND (internal pull-up); SENS- A7 to GND (R18)"
    pins:
      "SW1.1": {func: pin, net: /SENS_PLUS}
      "SW1.2": {func: gnd, net: /GND}
      "SW2.1": {func: pin, net: /SENS_MINUS}
      "SW2.2": {func: gnd, net: /GND}

  MOUNTING:
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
